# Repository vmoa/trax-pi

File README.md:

# T-Rax Raspberry Pi Notes

This is the Raspberry Pi implementation of the T-Rax roof controller for the Robert Ferguson Observatory
[rfo.org](https://rfo.org).

This design is a logical follow-on to the [Arduino T-Rax](https://github.com/votmoa/trax-arduino) roof controller
created back in 2017 by Jim Finn, David Kensiski and Jay Pacheco.  The switch to the Raspberry Pi was driven by the desire
to implement an [ASCOM Alpaca](https://ascom-standards.org/Developer/Alpaca.htm) interface so that the roof
can be opened via automation through tools such as [NINA](https://nighttime-imaging.eu/) and the now defunct [ACP](https://acpx.dc3.com/)

Testing insturctions can be found in the [test plan](doc/TestPlan.md) document.

Version history can be found in [VERSION.md](VERSION.md).

# Table of Contents

1. [Theory of Operation](#theory-of-operation)
1. [Detailed Design](#detailed-design)
1. [Hardware Design](#hardware-design)
1. [Future Plans](#future-plans)
1. [Installation](#installation)
1. [GPIO Notes](#gpio-notes)

# Theory of Operation

The server is written in Python 3 and utilizes only two external libraries:
[GPI Zero](https://gpiozero.readthedocs.io/en/stable/) to control the Raspberry Pi GPIO ports, and
[Flask](https://flask.palletsprojects.com/en/1.1.x/) to manage the web interface.  (Though Flask
has a bunch of prerequisites that also need to be loaded.)
The Browser panel is written in [HTML](https://www.w3schools.com/html/default.asp) using
Cascading Style Sheets ([CSS](https://www.w3schools.com/css/default.asp)) to control the apperance of the page, and
[Javascript](https://www.w3schools.com/js/default.asp) to handle communication and control the modal dialogs.

The overall software design is driven through interrupts -- there is no "main loop" as there was in the Arduino.
On start, the server sets  up logging, initializes each of the
GPIO pins, registers the web interface callbacks, then hands operation over to Flask to listen for incoming requests.

A separate bridge in `alpaca.py` exposes a minimal ASCOM Alpaca dome/shutter interface for automation clients. It accepts
`OpenShutter` and `CloseShutter` commands, reports `ShutterStatus`, and keeps control logic consistent with the browser
UI by routing Alpaca actuation through the same safety-checked roof toggle path.  Many thanks to
[Lena](https://github.com/lena-allie) for her [contributions](https://github.com/elenasch-playground/trax-pi/pull/1)
to the Alpaca driver.

There are three flavors of threads:

* Hardware input state changes trigger GPI Zero callbacks that execute in individual threads.
* Browser reqeusts trigger Flask actions that execute in separte threads.
* Finally an "update" thread executes every second to perform household chores.

There is a static html launcher page that is currently served directly by Apache.  This sets browser window size
(I don't think a window can reliably change its size once launched) and points it at http://trax:5000 which is where
trax.py is listening (by way of Flask).  This sends a template web page to paint the browser.  Once painted,
Javascript in the browser connects back to trax and and set up a server-sent events channel
([SSE](https://developer.mozilla.org/en-US/docs/Web/API/Server-sent_events))
so the server can pro-actively update the browser.  Browser javascript listens on this channel and paints the
display appropriately.  Browser buttons trigger async HTTP calls to varioius
trax URIs that perform an appropriate action, which in turn triggers an SSE response.

Breaking this down, the connection flow is as follows:

1. User connects to http://trax and clicks the "Launch" button
1. Browser launches the T-Rax browser window pointing to http://trax:5000
1. Server sends static HTML, CSS and Javascript to paint the browser
1. After panting, browser javascript connects to http://trax:5000/connect to set up SSE channel

Then in normal operation:

* Server sends events via SSE when something changes
  * Browser executes javascript to handle the event
* Browser buttons send HTTP asynchronous requests to http://trax:5000/{whatever} to trigger actions
  * Sever performs the actions and responsds via SSE

The update thread is simply a thread that runs on startup to perform household chores and proactively update the
browser.  It then reschedules itself to run again one second later.  This thread updates the clock on the T-Rax
page to act as a hardbeat to confirm the server/browser SSE channel is active

# Software Design

The T-Rax software is structured around a Flask-based HTTP interface, GPIO abstractions, and a small set of cooperating threads.

* `trax.py` is the entry point. It initializes logging, constructs the GPIO objects, starts the periodic update thread, and registers the Flask routes for browser and Alpaca clients.
* `device.py` wraps `gpiozero` inputs and outputs in `Sensor` and `Control` classes. Inputs are configured with callbacks, and outputs include toggle timing and fob motion retry logic.
* `browser.py` implements the web UI callbacks. Each browser action checks safety interlocks, performs the required GPIO actuation, and sends status updates to the browser via SSE.
* `alpaca.py` implements a minimal ASCOM/Alpaca dome/shutter interface. It exposes `OpenShutter`, `CloseShutter`, `ShutterStatus`, discovery, and management endpoints while reusing the same roof safety and toggle logic as the browser UI.
* `sse.py` manages the server-sent event channel. The browser connects to `/connect` and receives live indicator updates, notices, and status changes.
* `test_mode.py` provides GPIO stubs for non-Pi environments so the software can run and be tested on a regular development machine.
* A recurring per-second housekeeping thread updates the browser clock, logs status, and handles timeouts (like laser auto-off).

Roof motion is coordinated by safety checks on building power, roof power, weather, mount park state, and the open/closed end-stop sensors. Both browser commands and Alpaca `OpenShutter`/`CloseShutter` flows delegate to the same underlying roof toggle path to keep behavior consistent.

# Hardware Design

The system is built around a [Raspberry Pi 3 B+](https://www.raspberrypi.org/products/raspberry-pi-3-model-b-plus/)
computer, though any Pi that sports the 40-pin GPIO header should work.  The header is routed to a custom circuit
board that splits out the GPIO inputs and outputs.  Output ports are fed to a 6-pin connetor that connects to the
relay board (see below).  Inputs are fed through RC low-pass filters (to reduce the effect
of electrical noise), current limiting resistors and optoisolators which ultimately deliver 3.3v to GPIO input ports.

External connectors are wired to jacks on a connecor board to maintain modularity.  Inputs are fed via an 8-pin
connector to the control board.  Outputs connect via a wiring harness from the 6-pin connector on the control board.
The roof and mount outputs directly feed relays to close a nomrally open circuit that in turn closes a relay circuit
in each of the remote roof and mount power controllers (not shown).

KiCad schematics and circuit board layout are available in the [KiCad](KiCad) subdirectory.
The full schematic is also available as a PDF: [TRax-Schematic.pdf](KiCad/TRax-Schematic.pdf)

### WeatherOK

This is the hardware signal from the [Boltwood Cloud Sensor](https://diffractionlimited.com/product/boltwood-cloud-sensor-ii/).
The configuration of the Clarity II software on the CCD PC determines what conditions trigger a weather alert.
The input feeds an optoisolator which triggers a GPIO port of the Raspberry Pi.  The Boltwood signal is active low
hence the name of the port is "weather OK".

### Mount Power

There are two ports used for the mount: mountPowerOut and mountPowerIn.  mountPowerOut triggers a
relay on the TRax Control Board which in turn closes a remote circuit in the Mount Power Controller under the telescope.
Power for that circuit comes from the Mount Power Controller.  The closing of that circuit triggers a relay in
the Mount Power Controller that powers the 12V supply that drives the mount.  A secondary contact on that relay 
closes the mountPowerIn circuit which is fed by 12V from the TRax Control Board.  That is fed through an optoisolator
to the GPIO port on the Raspberry Pi to provide positive feedback of mount power.

### Roof Power

Similarly there are two ports used for roof power: roofPowerOut and roofPowerIn.  These are designed
virtually identically to the mount power ports described above.

### Open / Close

Mounted on the roof rails are magnetic reed relays (alarm sensors) that engage when the roof is
either fully open or fully closed.  The TRax Control Board provides 12V to these relays through the Open/Close port.
Singal from these are fed through optoisolators to the GPIO ports on the Raspberry Pi.

### Fob

The fob is an actual gate controller fob (Model LM123) that has been removed from it's case and wired to a terminal
block.  T-Rax provides the fob with 12v DC to "replace" the battery, and has the contacts from it's top button wired
so we can trigger the fob on command.  This trigger was orignally wired to a relay but the contact bounce caused
the fob to trigger several times when the relay was engaged.  We instead use an optoisolator which avoids the
bounce, but care must be taken to maintain polarity with respect to the isolator.  The button is also an active
part of an RF circuit (433.92 MHz) so cable length should be limited.

### Park Detector

Because there is no place on the mount where physical relays can be mounted to postively confirm
park position, we have built a laser park sensor.  This consists of a low power laser on the mount dovetail plate and
a corresponding laser detector attached to the north wall.  These are aligned so that the detector triggers only when
the mount is in park position.  Both laser and detector are connected to the park port through an RJ-11 splitter.

The laser output from the control board triggers a relay with provides 12vdc (switched) to the park connector.
This 12v powers voltage regulators in both moduels that provides the 5v necessary to power the devices.  When
power is applied, the laser illuminates while simultaneously the park detector powers up.  If the telescope is
parked, the beam of the laser illuminates the detector.  The detector is active low so the signal is inverted by
a 2N2222 transistor and triggers an optoisolator which closes the park input.  If the telescope is not parked,
the laser does not illuminate the detector and the optoisolator output remains open.

Using 12v to power 5v circuitry avoids the issue of voltage drop over long DC runs that we've seen with the "friggin' laser".

### Building Power

Since TRax is fed via UPS power, the building power port is fed by a 12V wall wart plugged into
a non-UPS powered outlet.  When there is a power failure, this voltage drops and we are able to detect the outage to
prevent opening (but not closing!) of the roof.  The 12V is fed through an optoisolator to the GPIO port on the
Raspberry Pi.  It should be noted that this entire 12V source is isolated from the rest of the TRax circuit.  The
input side of the optoisolator is feed directly from this 12V source and (unlike the other circuits) is *not*
connected to the Control Board ground.

### Heart & Power LEDs

The heartbeat LED is fed directly from a GPIO port on the Raspberry Pi (through a current limiting resistor) and
flashes to indicate that the TRax software is running and healthy.  The power LED is fed by the 3.3V power rail on
the Raspberry Pi (thorugh a current limiting resistor) and indicates that the Raspberry Pi has power.

### Grove LCD

This port is wired for the [I2C](https://www.circuitbasics.com/basics-of-the-i2c-communication-protocol/)
serial bus required by the [Grove RGB LCD](https://wiki.seeedstudio.com/Grove-LCD_RGB_Backlight/).  We route the `SDA`
and `SCL` ports from the Raspberry Pi as well as the requisite ground and +5V.  Note that this uses +5V, not the +3.3V
of the rest of the controller.

As of this writing the Python code does not yet implement the Grove LCD.

# Future Plans

- [ ] Use md5 hashed password instead of hard coding
- [ ] Implement all logging using Flask's logging wrapper (evaluate how useful)
- [ ] Switch from Flask web server to Apache/WCGI
- [ ] Implement ASCOM/Alpaca
- [ ] Implement the Grove LCD
- [ ] Make multi-user (eg: for emergency override, notifications)

## Notes on the ASCOM/Alpaca implementation

From: Roger Boulanger <rogerjb88@gmail.com>\
Date: Fri, Sep 19, 2025 at 2:40 PM\
Subject: East Wing Automation.\
To: David Kensiski <David@kensiski.org>\

Hi Dave:

Following our brief discussion on this subject a couple days ago, I'd like to confirm a couple things.

First, T-Rax will need to include a Dome Alpaca Server which accepts "OpenShutter" and "CloseShutter" commands to open & close the roof.

In addition, it will need to expose the ShutterStaus ("ShutterOpen" or "ShutterClosed"). While NINA will send out Discord notifications for both conditions, it will only look for a "ShutterOpen" condition before attempting to do anything with the telescope.

How do you feel about having T-Rax automatically turning on Mount Power whenever the roof is fully open and off when it isn't? Otherwise we'd have to use one of the other standard ASCOM Dome commands to do this from NINA. Not impossible but just a little weird.

A benefit to SkyX users would be one less Checklist step to execute;-)

Roger

# Installation

Installation instructions reside in their own file: [INSTALL.md](INSTALL.md)

# GPIO Notes

General Purpose Input/Output

## Input GPIO ports (sensors)

* GPIO4: weatherOK = newSensor(pin=4);
* GPIO17: bldgPowerIn = newSensor(pin=17);
* GPIO27: roofPowerIn = newSensor(pin=27);
* GPIO22: mountPowerIn = newSensor(pin=22);
* GPIO23: roofOpen = newSensor(pin=23);
* GPIO24: roofClosed = newSensor(pin=24);
* GPIO25: mountParked = newSensor(pin=25);

## Output GPIO ports (controls)

* GPIO5: roofPowerOut = newControl(pin=5)
* GPIO6: mountPowerOut = newControl(pin=6)
* GPIO26: fobOutput = newControl(pin=26)
* GPIO13: heartLed = newControl(pin=13)
* GPIO16: laserPowerOut = newControl(pin=16)

| GPIO | Function | T-Rax |
| ---- | -------- | ----- |
| 2    | I2C      | LCD   |
| 3    | I2C      | LCD   |
| 4    |          | weatherOK |
| 17   | SPI1     | bldgPowerIn |
| 27   |          | roofPowerIn |
| 22   |          | mountPowerIn |
| 10   | SPI0     |  |
| 9    | SPI0     |  |
| 11   | SPI0     |  |
| 0    | I2C      | LCD   |
| 5   |           | roofPowerOut |
| 6   |           | mountPowerOut |
| 13   | PWM      | Heart LED |
| 19   | PWM,SPI1 |  |
| 26   |          | fobOutput |
| | | |
| 14   | Serial   |  |
| 15   | Serial   |  |
| 18   | PWM,SPI1 |  |
| 23   |          | roofOpen |
| 24   |          | roofClosed |
| 25   |          | mountParked |
| 8    | SPI0     |  |
| 7    | SPI0     |  |
| 1    | I2C      | LCD   |
| 12   | PWM      |  |
| 16   | SPI1     | laserPowerOut |
| 20   | SPI1     |  |
| 21   | SPI1     |  |

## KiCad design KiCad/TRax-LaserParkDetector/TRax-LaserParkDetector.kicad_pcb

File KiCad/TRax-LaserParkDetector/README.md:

# Park Detector KiCad files

This is a static copy of the [TRax-Schematic](../TRax-Schematic) project at v1.7 with everythig stripped
out except for the park detector.  Reason being that KiCad doesn't appear to have a way to lay out a board
based on only part of a schematic.

**Caveat Emptor**: Changes made to the main schematic will have to be replicated here.  (Boo...)

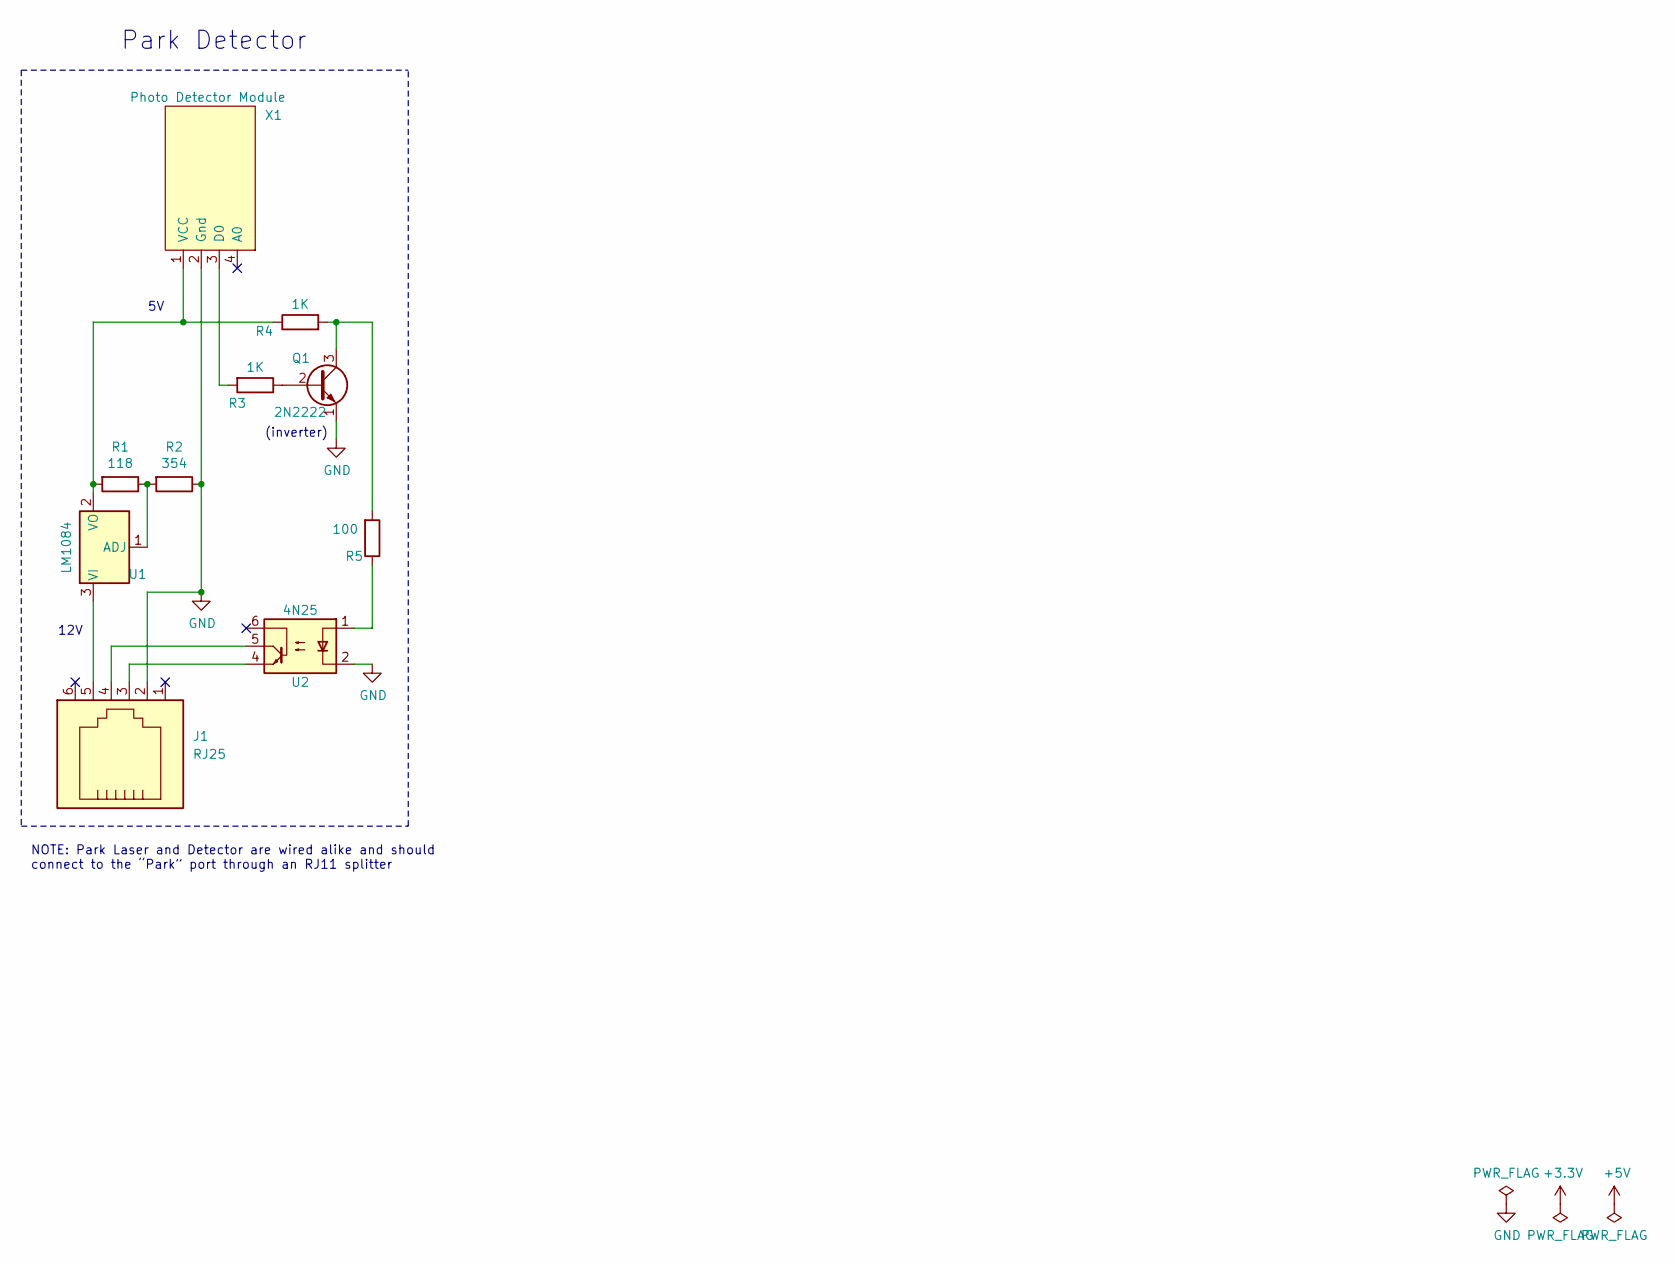
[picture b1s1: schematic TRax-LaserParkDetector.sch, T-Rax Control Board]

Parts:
J1: RJ25; PinHeader_1x06_P2.54mm_Vertical
Q1: 2N2222; TO-92_Inline
R1: 118; R_Box_L8.4mm_W2.5mm_P5.08mm
R2: 354; R_Box_L8.4mm_W2.5mm_P5.08mm
R3, R4: 1K; R_Box_L8.4mm_W2.5mm_P5.08mm
R5: 100; R_Box_L8.4mm_W2.5mm_P5.08mm
U1: LM1084; TO-220F-3_Vertical
U2: 4N25; DIP-6_W7.62mm
X1: Photo Detector Module; PhotoDetectorModule

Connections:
GND: J1.2, Q1.1 (E), R2.1, U2.2, X1.2 (Gnd)
unnamed: J1.3, U2.4
unnamed: J1.4, U2.5
unnamed: J1.5, U1.3 (VI)
unnamed: Q1.2 (B), R3.1
unnamed: Q1.3 (C), R4.2, R5.2
unnamed: R1.1, R2.2, U1.1 (ADJ)
unnamed: R1.2, R4.1, U1.2 (VO), X1.1 (VCC)
unnamed: R3.2, X1.3 (D0)
unnamed: R5.1, U2.1

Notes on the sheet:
Park Detector
12V
(inverter)
NOTE: Park Laser and Detector are wired alike and should connect to the “Park” port through an RJ11 splitter

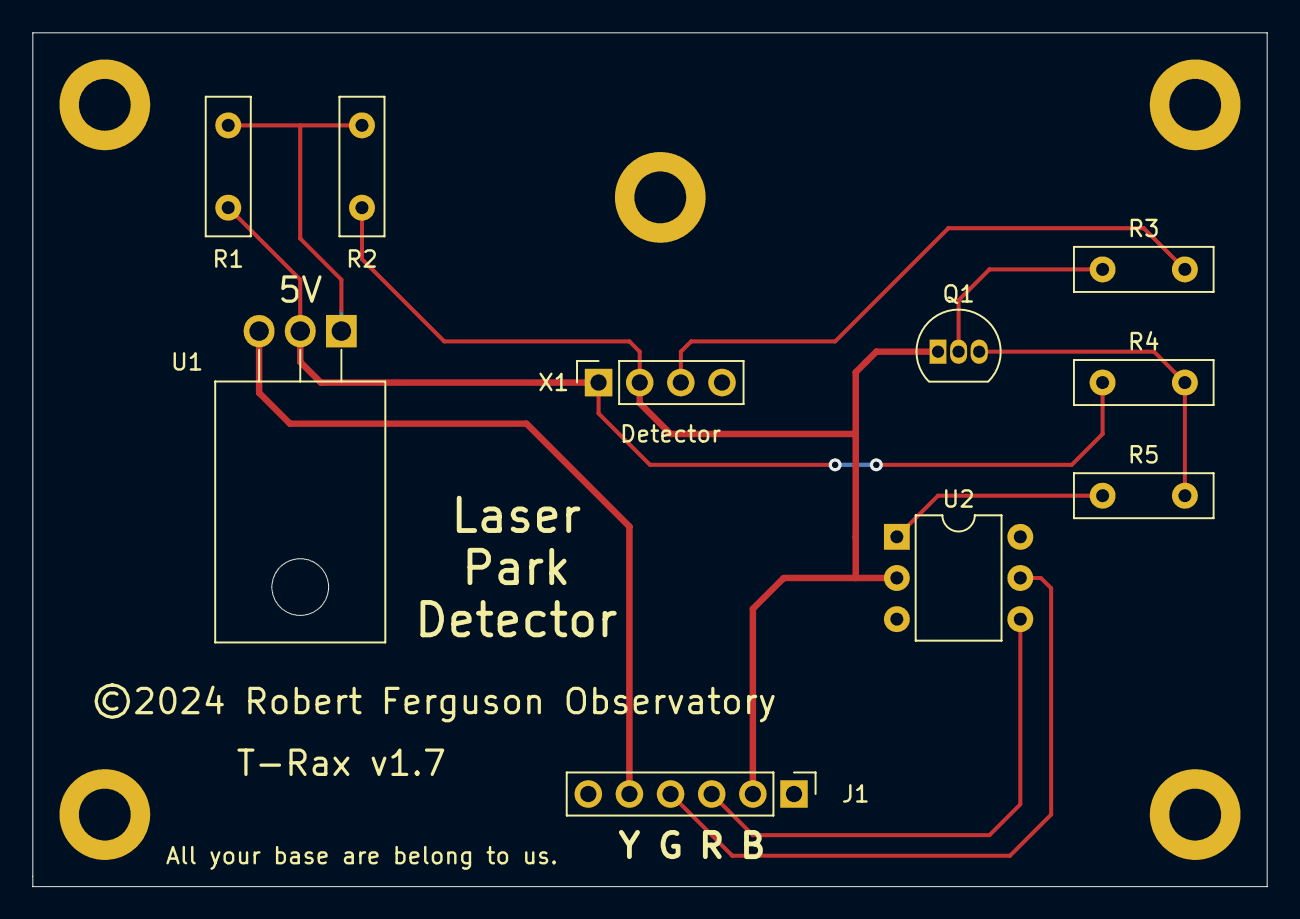
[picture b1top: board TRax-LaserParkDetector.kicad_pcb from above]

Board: 2 copper layers, 76.2 x 52.7 mm, 10 parts (0 on the bottom side), 10 nets.

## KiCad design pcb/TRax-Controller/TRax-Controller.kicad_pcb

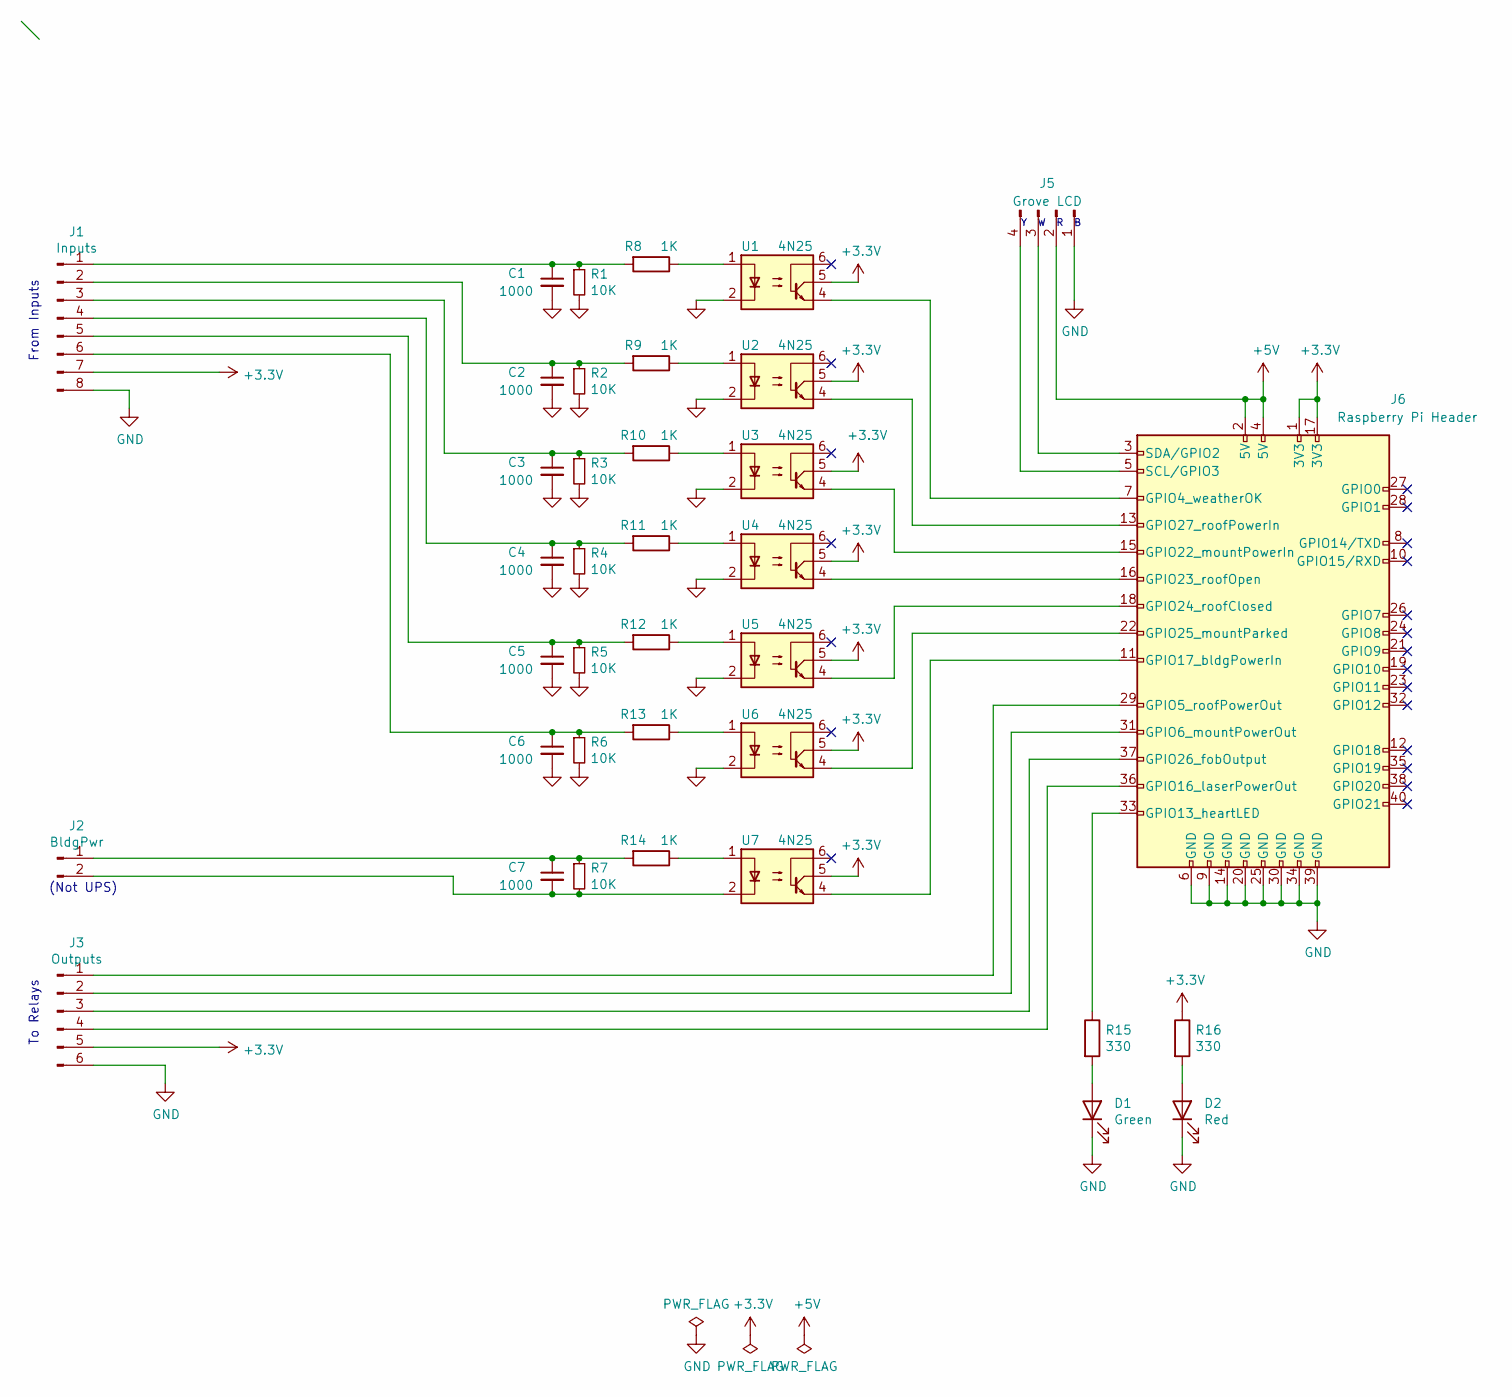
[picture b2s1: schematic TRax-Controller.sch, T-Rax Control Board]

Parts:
C1, C2, C3, C4, C5, C6, C7: 1000; C_Disc_D4.7mm_W2.5mm_P5.00mm
D1: Green; LED_D5.0mm
D2: Red; LED_D5.0mm
J1: Inputs; JST_XH_B8B-XH-A_1x08_P2.50mm_Vertical
J2: BldgPwr; JST_XH_B2B-XH-A_1x02_P2.50mm_Vertical
J3: Outputs; JST_XH_B6B-XH-A_1x06_P2.50mm_Vertical
J5: Grove LCD; JST_XH_B4B-XH-A_1x04_P2.50mm_Vertical
J6: Raspberry Pi Header; PinHeader_2x20_P2.54mm_Vertical
R1, R2, R3, R4, R5, R6, R7: 10K; R_Axial_DIN0207_L6.3mm_D2.5mm_P10.16mm_Horizontal
R8, R9, R10, R11, R12, R13, R14: 1K; R_Axial_DIN0207_L6.3mm_D2.5mm_P10.16mm_Horizontal
R15, R16: 330; R_Axial_DIN0207_L6.3mm_D2.5mm_P10.16mm_Horizontal
U1, U2, U3, U4, U5, U6, U7: 4N25; DIP-6_W7.62mm

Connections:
+3V3: J1.7, J3.5, J6.1 (3V3), J6.17 (3V3), R16.1, U1.5, U2.5, U3.5, U4.5, U5.5, U6.5, U7.5
+5V: J5.2, J6.2 (5V), J6.4 (5V)
GND: C1.2, C2.2, C3.2, C4.2, C5.2, C6.2, D1.1 (K), D2.1 (K), J1.8, J3.6, J5.1, J6.6 (GND), J6.9 (GND), J6.14 (GND), J6.20 (GND), J6.25 (GND), J6.30 (GND), J6.34 (GND), J6.39 (GND), R1.2, R2.2, R3.2, R4.2, R5.2, R6.2, U1.2, U2.2, U3.2, U4.2, U5.2, U6.2
unnamed: C1.1, J1.1, R1.1, R8.2
unnamed: C2.1, J1.2, R2.1, R9.2
unnamed: C3.1, J1.3, R3.1, R10.2
unnamed: C4.1, J1.4, R4.1, R11.2
unnamed: C5.1, J1.5, R5.1, R12.2
unnamed: C6.1, J1.6, R6.1, R13.2
unnamed: C7.1, J2.1, R7.1, R14.2
unnamed: C7.2, J2.2, R7.2, U7.2
unnamed: D1.2 (A), R15.2
unnamed: D2.2 (A), R16.2
unnamed: J3.1, J6.29 (GPIO5_roofPowerOut)
unnamed: J3.2, J6.31 (GPIO6_mountPowerOut)
unnamed: J3.3, J6.37 (GPIO26_fobOutput)
unnamed: J3.4, J6.36 (GPIO16_laserPowerOut)
unnamed: J5.3, J6.3 (SDA/GPIO2)
unnamed: J5.4, J6.5 (SCL/GPIO3)
unnamed: J6.7 (GPIO4_weatherOK), U1.4
unnamed: J6.11 (GPIO17_bldgPowerIn), U7.4
unnamed: J6.13 (GPIO27_roofPowerIn), U2.4
unnamed: J6.15 (GPIO22_mountPowerIn), U3.4
unnamed: J6.16 (GPIO23_roofOpen), U4.4
unnamed: J6.18 (GPIO24_roofClosed), U5.4
unnamed: J6.22 (GPIO25_mountParked), U6.4
unnamed: J6.33 (GPIO13_heartLED), R15.1
unnamed: R8.1, U1.1
unnamed: R9.1, U2.1
unnamed: R10.1, U3.1
unnamed: R11.1, U4.1
unnamed: R12.1, U5.1
unnamed: R13.1, U6.1
unnamed: R14.1, U7.1

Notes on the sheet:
(Not UPS)
Y W R B
From Inputs
To Relays

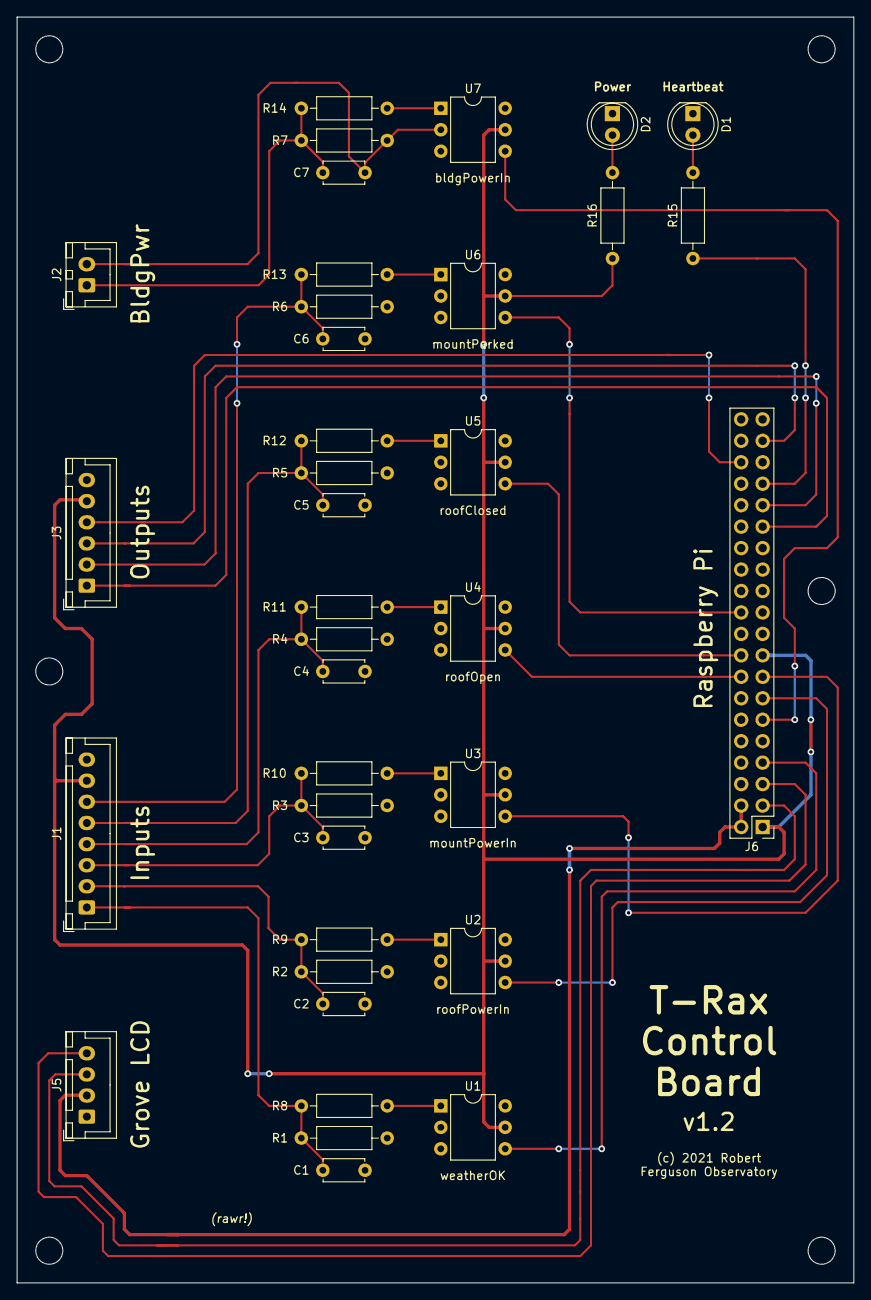
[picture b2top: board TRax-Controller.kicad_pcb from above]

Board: 2 copper layers, 99.1 x 149.9 mm, 37 parts (0 on the bottom side), 34 nets.

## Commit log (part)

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2021-03-13 added
2021-03-13 configure active low output pins
2021-03-13 formatting
2021-03-14 cleaned up test code
2021-03-16 split Sensor and Control into device.py
2021-03-16 moved printStatus to util.py
2021-03-16 changed dict names
2021-03-16 add pycache
2021-03-17 inegrated test mode into main code
2021-03-17 integrated into test-mode.py
2021-03-20 cleaned up references; moved printStatus to device; other misc
2021-03-21 add pinout diagram
2021-03-21 made image local cuz remote renders as a stream
2021-03-21 added some pretty words
2021-03-21 fixed ACP link
2021-03-21 fixed some formatting
2021-03-25 created Logger; created TraxGpio; much scope twiddling
2021-03-29 mixed fobOutput pin
2021-03-30 added centering
2021-03-30 finished hard coded page layout
2021-04-02 started Flask web server
2021-04-04 switched to threading rather than signals
2021-04-04 update template; started work on callback
2021-04-04 ignore foo file
2021-04-04 switched from custom logger.py to standard logging module
2021-04-06 checkpoint: working with limited standalone functionality
2021-04-06 checkpoint: cleaned up functions and names
2021-04-08 moved flask code into trax.py
2021-04-08 checkpoint: implemented JS update_indicator(); moved updates to printStatus()
2021-04-10 checkpoint: housekeeping phase 1
2021-04-10 refactored browser callbacks into browser.py
2021-04-10 added toggle functionality
2021-04-10 made buttons work (with placeholder functions)
2021-04-11 button callbacks functioning but no safety controls
2021-04-11 added ticker to free up notice area
2021-04-12 restored weather pin... again! ???
2021-04-12 replicated Arduino safety logic
2021-04-12 device callbacks update browser status and log
2021-04-12 moved to templates
2021-04-13 added --simulator arg
2021-04-13 Refactored devices to all be inside Gpio class
2021-04-14 add isParked() laser logic
2021-04-16 added park laser check and decay
2021-04-17 split out checkPark() and isParked(); switch to park enum
2021-04-20 refactored css and js into static files
2021-04-20 added static launcher page
2021-04-24 cleaned up css
2021-04-25 added emergency override interface (html,css,js and python)
2021-04-26 cleaned up park communication
2021-04-26 bumped version to 1.0
2021-04-26 started on design doc
2021-04-27 added 3D Print plans from Jay
2021-04-27 reworded
2021-04-27 gave Jay credit
2021-04-30 cleaned up style; reindented
2021-05-01 added T-Rex clipart
2021-05-03 finished general theory
2021-05-04 checkpoint
2021-05-05 started hardware design
2021-05-10 added hardware design
2021-05-12 added KiCad files (schematics, pcb layout)
2021-05-12 added KiCad exceptions
2021-05-12 renamed pcb directory
2021-05-12 bumped schematic version, cleaned up
2021-05-12 added block diagram placeholders
2021-05-12 added KiCad readme
2021-05-17 add file locking to prevent multiple copies
2021-05-27 ignore Gerber files
2021-05-27 switch to 6P6C connectors; misc cleanup
2021-05-27 relays schematic v1.2b
2021-06-05 added connection count to ticker
2021-06-05 created service start script
2021-06-05 installation instructions
2021-06-05 bumped version
2021-06-05 pass version to browser and report on connect
2021-06-24 pulled custom relay symbol into library
2021-07-03 mount and roof should not be reverse logic
2021-07-04 added test plan
2021-07-07 removed pedantic power checks
2021-07-07 bump version
2021-07-10 updated installation instructions
2021-07-10 renamed file
2021-07-11 added toggleThrice()
2021-07-11 added toggleThrice to make sure fob activates roof
2021-07-11 reconstructed version and created VERSION.md
2021-07-11 tweak installation instructions
2021-07-11 added version history
2021-07-17 fix red/black wiring on input RJ11s
2021-08-22 v1.0.5: in emergency override, checkPark toggles laser indefinitely, and updateBrowser reports actual park position
2021-08-23 in emergency override, checkPark toggles laser indefinitely, and updateBrowser reports actual park position
2021-09-28 Revert "bump version"
    This reverts commit 960fc378857c819416aefac2ec4f12e1e89098eb.
2021-09-28 added toggleFob(), roofPosition()
2021-09-28 replace toggleThrice() with toggleFob()
2021-09-28 removed toggleThrice(); added logging and notification to toggleFob(); fixed bugs
2021-09-28 bumped version to v1.0.6rc1
2021-09-28 RELEASE v.1.0.6: Replace toggleThrice() with fob.toggleFob(), using callbacks instead of a timer loop
2021-10-17 Fixed toggleFob() roof logic; Added "confused" roof state
2021-10-17 Increased fob_wait to 3 seconds; Better roof position reporting; Added "confused" roof state
2021-10-17 Added "confused" roof state
2021-10-17 bumped version to 1.0.7
2021-10-18 merged all there schematics into one
2021-10-18 Updated revision history and printed to pdf
2021-10-18 Updated revision history
2021-10-18 cleaned up pre-merge docs
2021-10-31 updated schematic (v1.7) direct wire fob isolator to fob tigger
2021-10-31 updated hardware documentation
2021-11-01 twiddled doc a bit
2023-06-21 bumped version to 1.0.8rc0; implement 120 second timeout for laser
2023-06-22 bumped version to 1.0.8; fixed laser timeout for Emergency Override
2024-03-01 add Laser Park Detector board layout
2025-04-23 simple boltwood query
2025-04-23 created class Weather
2025-04-25 Test program obs_conditions.py
    Connects to Boltwood and returns humidity, pressure, temperature
    and dewpoint
2025-09-19 alpaca automation notes
2026-05-30 add a minimal ASCOM Alpaca dome driver to control the roof (with GitHub copilot GPT-5 help)
2026-06-01 Add CLAUDE.md to trax-pi repository
2026-06-13 alpaca: add roof and mount power logic to _{open,close}shutter()
2026-06-13 alpaca: add discovery and apiversion endpoints
2026-06-13 alpaca: improve discovery; add multicast responder
2026-06-14 alpaca: add configureddevices endpoint
2026-06-14 rebase
2026-06-14 bumped version to 1.1.0
2026-06-14 alpaca: claude was hallucinating multicast; switch to udp broadcast
2026-06-14 fix debug logging (I hope!)
2026-06-14 alpaa: implement /management/apiversion

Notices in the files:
KiCad/TRax-LaserParkDetector/TRax-LaserParkDetector.kicad_pcb:
©2024 Robert Ferguson Observatory
pcb/TRax-Controller/TRax-Controller.kicad_pcb:
(c) 2021 Robert
